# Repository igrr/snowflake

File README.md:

Snowflake, a New Year Souvenir
------------------------------

These were small New Year souvenirs I've made for my friends and family.

Snowflake shaped piece of laser cut acrylic with a small PCB in the center. PCB has 6 right angle mounted LEDs illuminating the inside of the acrylic sheet. LEDs are driven by the microcontroller, which uses PWM to make LEDs glow in a pseudo random way. One button, connected to the reset pin of the microcontroller, is used to turn on and turn off the device.

### Laser cut shapes

`lasercut` directory contains a Sketchup file with two snowflake shapes.

### PCB

`pcb` directory contains the schematic and PCB layout made in Eagle CAD.

### Firmware

`firmware` directory contains the program for the STM8L051F3 MCU. To build it:
- install [SDCC](https://sourceforge.net/projects/sdcc) and add it to the `PATH`
- run `git submodule update --init` to get libstm8 submodule
- go to `firmware` directory and run `make`

[stm8flash](https://github.com/vdudouyt/stm8flash) wan used to flash the firmware to the MCU. Compile it, and add it to the `PATH`. Then run `make flash` in `firmware` directory.

### Parts used

- LEDs: https://item.taobao.com/item.htm?id=525144507380
- 0603 1k resistors
- CR1220 battery: https://item.taobao.com/item.htm?id=521527440135
- STM8L051F3P6 MCU: https://detail.tmall.com/item.htm?id=40540345444

### License

All files in this repository (except libstm8 submodule) are distributed under CC0 license.

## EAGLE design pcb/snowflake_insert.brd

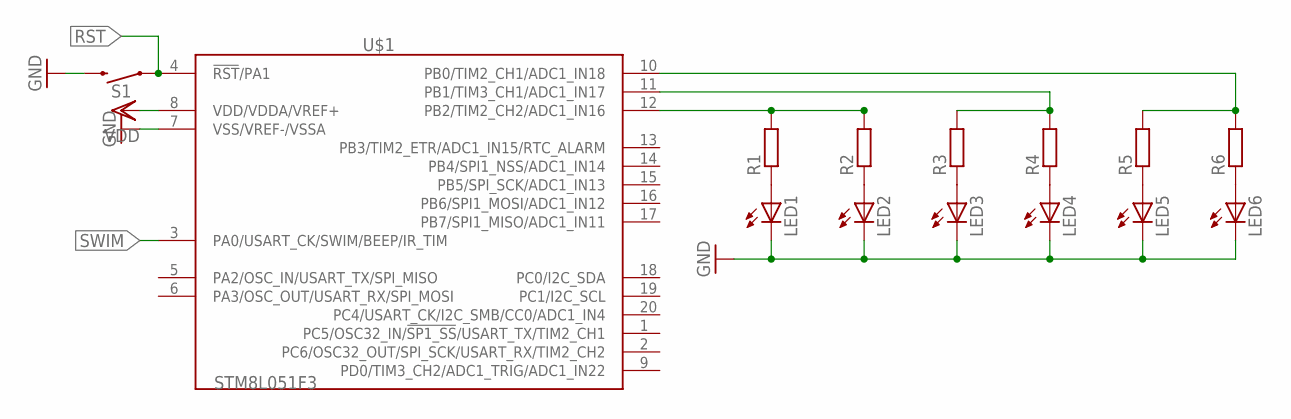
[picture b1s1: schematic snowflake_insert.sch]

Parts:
LED1, LED2, LED3, LED4, LED5, LED6: LEDSML0805; SML0805
R1, R2, R4, R5, R6: R-EU_R0603; R0603
R3: R-EU_R0402; R0402
S1: MOMENTARY-SWITCH-SPST-SMD-6.0X3.5MM; TACTILE_SWITCH_SMD_6.0X3.5MM
U$1: STM8L051F3; TSSOP20

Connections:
GND: LED1.C, LED2.C, LED3.C, LED4.C, LED5.C, LED6.C, S1.2, U$1.7 (VSS/VREF-/VSSA)
unnamed: LED1.A, R1.1
unnamed: LED2.A, R2.1
unnamed: LED3.A, R3.1
unnamed: LED4.A, R4.1
unnamed: LED5.A, R5.1
unnamed: LED6.A, R6.1
unnamed: R5.2, R6.2, U$1.10 (PB0/TIM2_CH1/ADC1_IN18)
unnamed: R3.2, R4.2, U$1.11 (PB1/TIM3_CH1/ADC1_IN17)
unnamed: R1.2, R2.2, U$1.12 (PB2/TIM2_CH2/ADC1_IN16)
RST: S1.1, U$1.4 (!RST!/PA1)
SWIM: U$1.3 (PA0/USART_CK/SWIM/BEEP/IR_TIM)
VDD: U$1.8 (VDD/VDDA/VREF+)

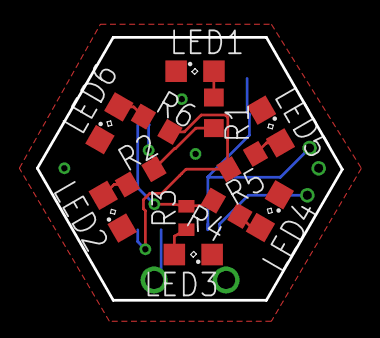
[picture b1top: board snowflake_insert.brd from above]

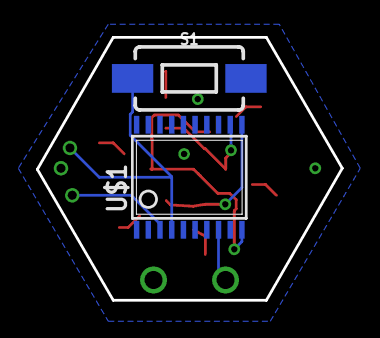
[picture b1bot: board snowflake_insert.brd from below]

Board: 2 copper layers, 16.9 x 14.6 mm, 14 parts (2 on the bottom side), 11 nets.

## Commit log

2018-01-01 initial and final version

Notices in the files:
parts and their libraries:
SparkFun-Switches: Licensing: Creative Commons ShareAlike 4.0 International - https://creativecommons.org/licenses/by-sa/4.0
